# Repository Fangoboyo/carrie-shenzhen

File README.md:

# Carrie 🥕 — Embedded Audio/Video Recording Smart Pen

An embedded audio-recording smart pen shaped like a carrot, featuring a custom pot docking station for charging and data transfer. Powered by the Luckfox Pico Mini B (RV1103).

BILL OF MATERIALS IS IN [docs](/docs)

---

## Project Overview

A personal carry device in the shape of a carrot, Carrie is an interpretation of the carrot pen used by Judy Hopps in Zootopia. It's built with a microphone and a camera, integrated into the tiny form factor of a pen, and powered by an embedded Linux microcontroller (Luckfox Pico Mini B) on a custom PCB. With the click of a button, Carrie records 1080p footage at 30 FPS with audio, making sure you never forget to record those memorable moments. Then, simply take off the cap and plug the pen into the pot docking station to transfer your video files to a host computer and charge Carrie's battery.

---

## Why?

All 4 of the team members of this project are High School seniors. At the end of the year, many of the people who we have spent a majority of our lives with will be leaving to colleges across the world. It's easy to say that you'll keep in touch and commit to sending pictures and videos often of what you do everyday, but it's often a promise that is neglected not from a lack of care, but from the nature of experiencing an event; your first thought isn't always to start recording. With a personal carry device in such a form factor, Carrie serves as an always present, physical reminder of that promise. In this way, it helps old friends reconnect and stay connected.

---

## Directory Structure

```
├── docs/                           # Project documentation, Zines, and planning
│   ├── planning/                   # Vault planning notes and Technical Canvas
│   │   ├── notes/                  # Detailed engineering notes (display, GPIO, recording, etc.)
│   │   └── technical_overview.canvas # Visual concept overview
│   ├── bill_of_materials.csv       # Master Bill of Materials (BOM) with links & costs
│   └── zine.pdf                    # Creative project documentation
├── hardware/                       # Mechanical and Electrical designs
│   ├── cad/                        # Fusion 360 & STEP models
│   │   ├── individual_parts/       # Separate CAD files for components
│   │   └── README.md               # CAD specific notes & instructions
│   └── pcb/                        # KiCad PCB designs
│       ├── battery_charger/        # Carrot power regulation and battery charger PCB
│       ├── carry/                  # Main controller and breakout board PCB
│       ├── dirt/                   # Pot wiring junction PCB (V1)
│       └── dirt2/                  # Pot wiring junction PCB (V2)
├── firmware/                       # Source code for microcontrollers
│   ├── carrot/                     # RV1103 C code (Camera, Audio, and GPIO controls)
│   └── pot/                        # ESP8266 display driver code (.ino)
├── materials/                      # Detailed component datasheet notes & summaries
│   ├── bms/                        # Battery Management System notes (MCP73831, DW01A, etc.)
│   ├── images/                     # Component reference photos
│   └── *.md                        # Individual parts summaries (LCD, Microphone, Pogo, etc.)
└── platform/                       # React frontend & PocketBase/Bun backend dashboard
```

---

## Step-by-Step Build & Replication Guide

Follow this guide to replicate both the carrot pen (Carrie) and the docking station (Pot).

---

### 1. Bill of Materials (BOM)
Refer to the detailed master [Bill of Materials](docs/bill_of_materials.csv) for pricing, sourcing links, and specifications.

*   **Compute (Pen):** [Luckfox Pico Mini B (RV1103)](materials/esp32.md) - Linux SBC
*   **Sensor (Pen):** [SC3336 3MP Camera Module](materials/lcd_display.md) (CSI interface)
*   **Audio (Pen):** [SPH0655 Digital MEMS Microphone](materials/microphone.md)
*   **Battery (Pen):** 3.7V 800mAh Li-ion battery (size 14500 cell)
*   **Power (Pen):** Custom charger PCB with [MCP73831T-2A Charger IC](materials/bms/mcp73831.md)
*   **Indicator (Pen):** SunLED XZVGMDK53W-9 (bi-color Red/Green SMD LED)
*   **Compute (Pot):** [ESP8266 Dev Board](materials/esp32.md) (Wemos D1 Mini or similar)
*   **Display (Pot):** [ILI9341 320x240 SPI Touchscreen Display](materials/lcd_display.md)
*   **Docking Junction:** 4-pin Magnetic Contact POGO pins (5V, GND, D+, D-)
*   **Enclosure:** Orange/Green PLA filament, PLA glue.

---

### 2. Schematics & Electrical Design
The electrical system is divided between the Pen and the Pot. Schematics can be reviewed inside the [KiCad PCB Projects](hardware/pcb/).

#### A. The Pen (Carrie)
The pen uses two PCBs:
1.  **Main Board (`hardware/pcb/carry/`):** Hosts the Luckfox Pico Mini B. Routes the camera CSI ribbon, digital MEMS microphone (SPH0655), recording button, and status indicator LEDs.
2.  **Battery Charger Board (`hardware/pcb/battery_charger/`):** Features the [MCP73831T](materials/bms/mcp73831.md) charge controller, protection circuit (DW01A + FS8205A), and matches the bottom shape of the pen where the 4 magnetic contact pads reside.

##### Main Compute Module: Embedded Luckfox Pico Mini B

| Luckfox Pico Mini B (2D Layout) | Luckfox Pico Mini B (3D Render) |
| :---: | :---: |
|  |  |

*Figure 2: The RV1103-based Luckfox Pico Mini B development board used as the central Linux-based camera controller.*

##### Input: Audio & Video

| Microphone Breakout | CSI Camera Module |
| :---: | :---: |
|  |  |

*Figure 3: Layouts for the digital SPH0655 MEMS Microphone and the SC3336 3MP CSI camera module.*

##### Power Management: MCP73831T-2A

| Charge Controller Chip | 2D Layout Routing | 3D Board Design |
| :---: | :---: | :---: |
|  |  |  |

*Figure 4: The custom power board containing the MCP73831 charge management IC and protection circuits to safely regulate the 14500 Li-ion battery.*

##### Status Indicator: SunLED XZVGMDK53W-9

*Figure 5: Bi-color (Red/Green) SMD status indicator LED for tracking recording states.*

---

#### B. The Pot (Docking Station)
The pot PCB (`hardware/pcb/dirt2/`) aggregates connections for the ESP8266 Dev Board, ILI9341 SPI Display, and a Y-Junction cable to split power and USB data signals.

##### Embedded ESP8266 Board

| 3D Model | 2D Design |
| :---: | :---: |
|  |  |

*Figure 6: Custom PCB interface housing the ESP8266, routing signals to the LCD and decoupling incoming USB lines.*

##### Display: ILI9341

*Figure 7: SPI Serial TFT display used to display system telemetry and connection feedback.*

---

### 3. CAD & Mechanical Assembly
All model assets are stored in [hardware/cad/](hardware/cad/).

#### The Shell

| Camera Side Cutout | Button Side Cutout |
| :---: | :---: |
|  |  |

*Figure 8: Outer mechanical CAD model of the carrot-shaped casing showing camera aperture and button positioning.*

#### Internals

*Figure 9: Exploded and internal CAD views highlighting the structural ribs, battery clip, and PCB slots inside the carrot pen.*

#### Flowerpot Dock

| Isometric View | Front Cutaway | Back Enclosure |
| :---: | :---: | :---: |
|  |  |  |

| Display Bezel Fitting | Base Enclosure Layout | Underneath Routing |
| :---: | :---: | :---: |
|  |  |  |

| Receptacle Neck Alignment | | |
| :---: | :---: | :---: |
|  | | |

*Figure 10: Assembly CAD breakdowns of the flowerpot dock housing the display, wiring channels, and internal board mounts.*

#### POGO Pins for Data Transfer
We use a magnetic, spring-loaded POGO pin port at the bottom interface of the carrot and inside the pot neck to route data and charge signals.

*Figure 11: The 4-pin magnetic layout routing 5V, GND, D+, and D- for toolless charging and storage connection.*

---

### 4. Firmware Build & Flashing Guide

#### A. Pen Firmware (RV1103)
The pen runs Buildroot Linux. Its C firmware is compiled inside a Docker Dev Container to manage target environment dependencies.

1.  **Launch Container:**
    Open the [firmware/carrot/](firmware/carrot/) directory in VS Code. It will prompt you to reopen in the dev container. Under the hood, this loads the `Dockerfile` from [firmware/carrot/.devcontainer/Dockerfile](firmware/carrot/.devcontainer/Dockerfile) which installs the cross-compiler toolchain `arm-rockchip830-linux-uclibcgnueabihf` and Rockchip Media Process Interface (RKMPI) headers.
2.  **Build Code:**
    Run the compile script:
    ```bash
    ./build.sh main
    ```
    This script cross-compiles:
    *   `main.c` (Core thread controller)
    *   `gpio/gpio.c` (Button interrupt and state control)
    *   `recorder/camera_recorder.c` (Uses RKMPI to fetch H.264 video streams from hardware framebuffers)
3.  **Deployment via ADB:**
    The script automatically runs `adb push` over the USB bridge to load the executable into the Luckfox:
    ```bash
    # Pushes binary and marks executable
    adb push main /root/
    adb shell "chmod +x /root/main"
    ```
    To test instantly, run:
    ```bash
    adb shell /root/main
    ```

#### B. Pot Display Firmware (ESP8266)
1.  Open the [firmware/pot/](firmware/pot/) folder in Arduino IDE.
2.  Install the **TFT_eSPI** library through the Library Manager.
3.  Copy/configure the correct pin assignments (CS, DC, RST, LED) in the `User_Setup.h` file located inside the `TFT_eSPI` library folder directory to match the ESP8266 pinout.
4.  Build and upload [displaydriver.ino](firmware/pot/displaydriver.ino) to your ESP8266 over serial USB.

---

### 5. Testing & Verification

1.  **Hardware Self-Test:** Connect the carrot pen to your PC. A solid green light indicates full charge; red/orange indicates active charging.
2.  **GPIO Check:** Run the compiled binary [gpio_input](firmware/carrot/gpio/gpio_input.c) to verify button state changes:
    ```bash
    ./build.sh gpio
    ```
3.  **Video Stream Test:** Run the `recorder` profile to verify image sensor capture and H.264 stream writing:
    ```bash
    ./build.sh recorder
    # Run on board: adb shell /root/camera_recorder_demo
    ```
4.  **Full Loop Recording:** Tap the physical button on the carrot casing. The indicator LED flashes to signal recording. Push the button again to stop.
5.  **Docking & Transfer:** Dock the pen in the Pot. The LCD screen should light up, showing connection telemetry. The PC will recognize a USB mass storage device or an ADB network interface. 
6.  **Web Dashboard Sync:** Start the React platform. Use the dashboard to fetch files from the docked pen and stream them directly onto Google Drive.
### Web Platform Dashboard
Okay I'm going to cut the formal documentation-speech for this part because im genuinely so proud of this website, it lets you plug your pot directly into your computer, and the browser is able to take the datastream from the USB and directly upload it to youtube for infinite free storage. All of the components are super animated like the books float and flip on their own, they rotate, they blur, all done with just tailwind. It genuinely took such a long time but adds an incredibly integrated aspect of the project that just brings everything together.

*Figure 1: React-based web dashboard displaying scrapbook video feeds synced from the carrot pen.*

For more details on the design, code operations, and custom hardware modules, see the docs folder, where obsidian canvases draw out everything overviewing the project.

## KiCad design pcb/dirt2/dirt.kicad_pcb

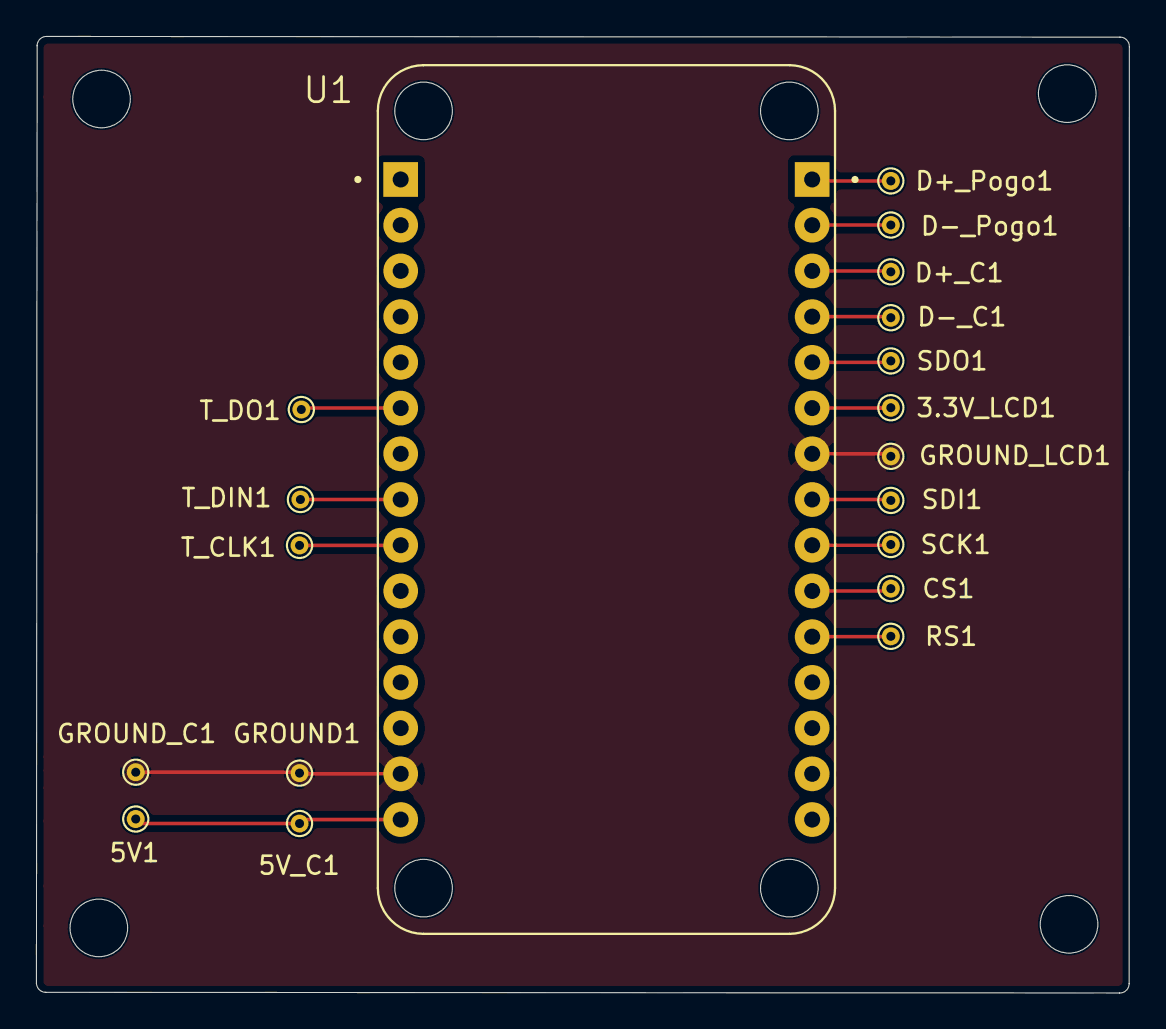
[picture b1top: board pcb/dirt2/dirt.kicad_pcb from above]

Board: 2 copper layers, 60.7 x 53.1 mm, 19 parts (0 on the bottom side), 15 nets.

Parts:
3.3V_LCD1: 3.3V Output to LCD; TestPoint_THTPad_D1.0mm_Drill0.5mm
5V1: 5V Output from Pogo; TestPoint_THTPad_D1.0mm_Drill0.5mm
5V_C1: 5V Input USB C; TestPoint_THTPad_D1.0mm_Drill0.5mm
CS1: TestPoint; TestPoint_THTPad_D1.0mm_Drill0.5mm
D+_C1: D+ FROM USB C; TestPoint_THTPad_D1.0mm_Drill0.5mm
D+_Pogo1: D+ FROM Pogo; TestPoint_THTPad_D1.0mm_Drill0.5mm
D-_C1: D- FROM USB C; TestPoint_THTPad_D1.0mm_Drill0.5mm
D-_Pogo1: D- FROM Pogo; TestPoint_THTPad_D1.0mm_Drill0.5mm
GROUND1: GND from Pogo; TestPoint_THTPad_D1.0mm_Drill0.5mm
GROUND_C1: GND from USB C; TestPoint_THTPad_D1.0mm_Drill0.5mm
GROUND_LCD1: GND to LCD; TestPoint_THTPad_D1.0mm_Drill0.5mm
RS1: TestPoint; TestPoint_THTPad_D1.0mm_Drill0.5mm
SCK1: TestPoint; TestPoint_THTPad_D1.0mm_Drill0.5mm
SDI1: TestPoint; TestPoint_THTPad_D1.0mm_Drill0.5mm
SDO1: TestPoint; TestPoint_THTPad_D1.0mm_Drill0.5mm
T_CLK1: TestPoint; TestPoint_THTPad_D1.0mm_Drill0.5mm
T_DIN1: TestPoint; TestPoint_THTPad_D1.0mm_Drill0.5mm
T_DO1: TestPoint; TestPoint_THTPad_D1.0mm_Drill0.5mm
U1: SEEED_113990105

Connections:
GND: GROUND1.1 (1_1), GROUND_C1.1 (1_1), GROUND_LCD1.1 (1_1), U1.J1_14 (GND), U1.J2_7 (GND)
unnamed: 3.3V_LCD1.1 (1_1), U1.J2_6 (3v3)
unnamed: T_CLK1.1 (1_1), U1.J1_9 (CLK)
unnamed: D+_Pogo1.1 (1_1), U1.J2_1 (D0)
unnamed: D-_Pogo1.1 (1_1), U1.J2_2 (D1)
unnamed: D+_C1.1 (1_1), U1.J2_3 (D2)
unnamed: D-_C1.1 (1_1), U1.J2_4 (D3)
unnamed: SDO1.1 (1_1), U1.J2_5 (D4)
unnamed: SDI1.1 (1_1), U1.J2_8 (D5)
unnamed: SCK1.1 (1_1), U1.J2_9 (D6)
unnamed: CS1.1 (1_1), U1.J2_10 (D7)
unnamed: RS1.1 (1_1), U1.J2_11 (D8)
unnamed: T_DIN1.1 (1_1), U1.J1_8 (SD0)
unnamed: T_DO1.1 (1_1), U1.J1_6 (SD1)
unnamed: 5V1.1 (1_1), 5V_C1.1 (1_1), U1.J1_15 (Vin)

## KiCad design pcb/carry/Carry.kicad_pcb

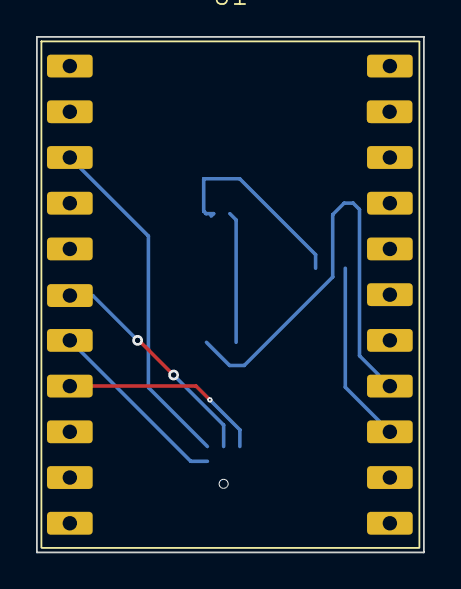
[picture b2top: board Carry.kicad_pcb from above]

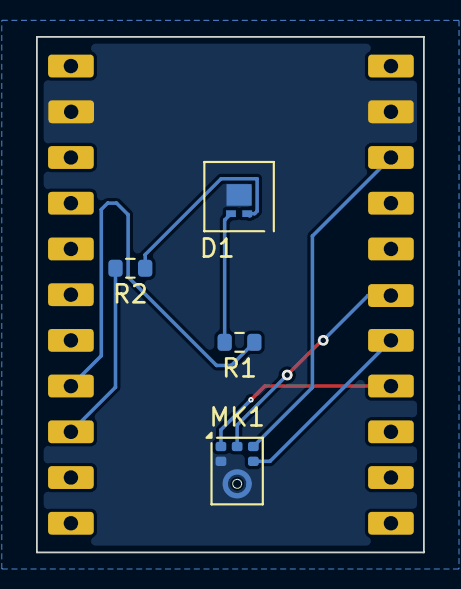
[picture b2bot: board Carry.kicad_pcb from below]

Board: 2 copper layers, 21.5 x 28.6 mm, 5 parts (4 on the bottom side), 9 nets.

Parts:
D1: LED_Dual_KKA; LED-L1T2_LUMILEDS
MK1: SPH0645LM4H; Knowles_SPH0645LM4H-6_3.5x2.65mm
R1, R2: 1k; R_0603_1608Metric
U1: Luckfox-Pico_Mini_B; Luckfox_Pico_Mini_B

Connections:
/MIC_DATA: MK1.6 (DATA), U1.6 (GPIO1_C0_d)
GND: D1.3 (K), MK1.2 (SEL), MK1.3 (GND), U1.2 (GND), U1.21 (GND)
unnamed: D1.1 (A1), R2.1
unnamed: D1.2 (A2), R1.2
unnamed: MK1.4 (BCLK), U1.7 (GPIO1_C1_d)
unnamed: MK1.5 (VDD), U1.3 (VCC_3V3)
unnamed: MK1.1 (WS), U1.8 (GPIO1_C2_d)
unnamed: R2.2, U1.14 (GPIO1_D2_d)
unnamed: R1.1, U1.15 (GPIO1_D3_d)

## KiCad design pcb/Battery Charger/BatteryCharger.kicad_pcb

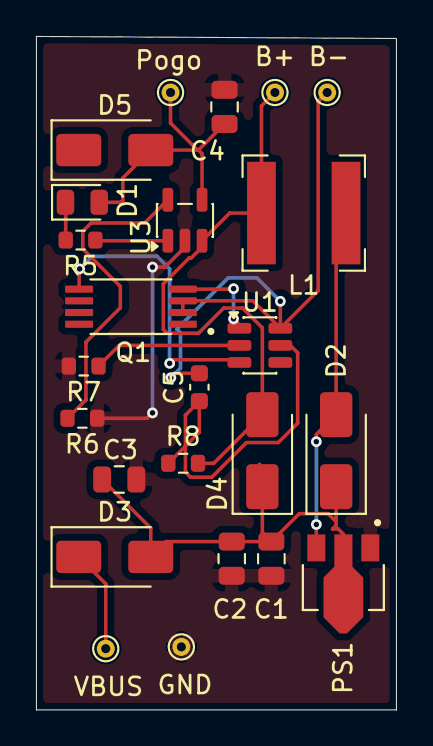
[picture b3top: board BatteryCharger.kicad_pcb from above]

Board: 2 copper layers, 20.0 x 37.4 mm, 24 parts (0 on the bottom side), 14 nets.

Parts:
B+: B+; TestPoint_THTPad_D1.0mm_Drill0.5mm
B-: B-; TestPoint_THTPad_D1.0mm_Drill0.5mm
C1, C2: 12; C_0805_2012Metric
C3, C4: 4.7; C_0805_2012Metric
C5: 0.1; C_0603_1608Metric
D1: LED; LED_0805_2012Metric
D2, D3, D4, D5: SS14; D_SMA
GND: B-; TestPoint_THTPad_D1.0mm_Drill0.5mm
L1: 22; L_Bourns-SRN6028
PS1: ME2108A33P
Pogo: Pogo+; TestPoint_THTPad_D1.0mm_Drill0.5mm
Q1: FS8205A
R5: 470; R_0603_1608Metric
R6: 2k; R_0603_1608Metric
R7: 1k; R_0603_1608Metric
R8: 100; R_0603_1608Metric
U1: DW01A; SOT-23-6
U3: MCP73831; SOT-23-5
VBUS: Output 5V; TestPoint_THTPad_D1.0mm_Drill0.5mm

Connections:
GND: C1.2, C2.2, C3.2, C4.2, GND.1 (1_1), PS1.1 (VSS), Q1.6, Q1.7, R6.1, R7.2, U3.2 (V_{SS})
unnamed: C4.1, D1.2 (A), D5.2 (A), Pogo.1 (1_1), U3.4 (V_{DD})
unnamed: D1.1 (K), R5.2
unnamed: D2.2 (A), L1.2, PS1.3 (LX)
unnamed: C1.1, C2.1, C3.1, D2.1 (K), D3.2 (A), D4.1 (K), PS1.2 (VOUT)
unnamed: D3.1 (K), D5.1 (K), VBUS.1 (1_1)
unnamed: B+.1 (1_1), D4.2 (A), L1.1, R8.1, U3.3 (V_{BAT})
unnamed: R7.1, U1.2 (CS)
unnamed: B-.1 (1_1), C5.2, Q1.2, Q1.3, U1.6 (GND)
unnamed: Q1.5, U1.3 (OC)
unnamed: Q1.4, U1.1 (OD)
unnamed: C5.1, R8.2, U1.5 (VCC)
unnamed: R6.2, U3.5 (PROG)
unnamed: R5.1, U3.1 (STAT)

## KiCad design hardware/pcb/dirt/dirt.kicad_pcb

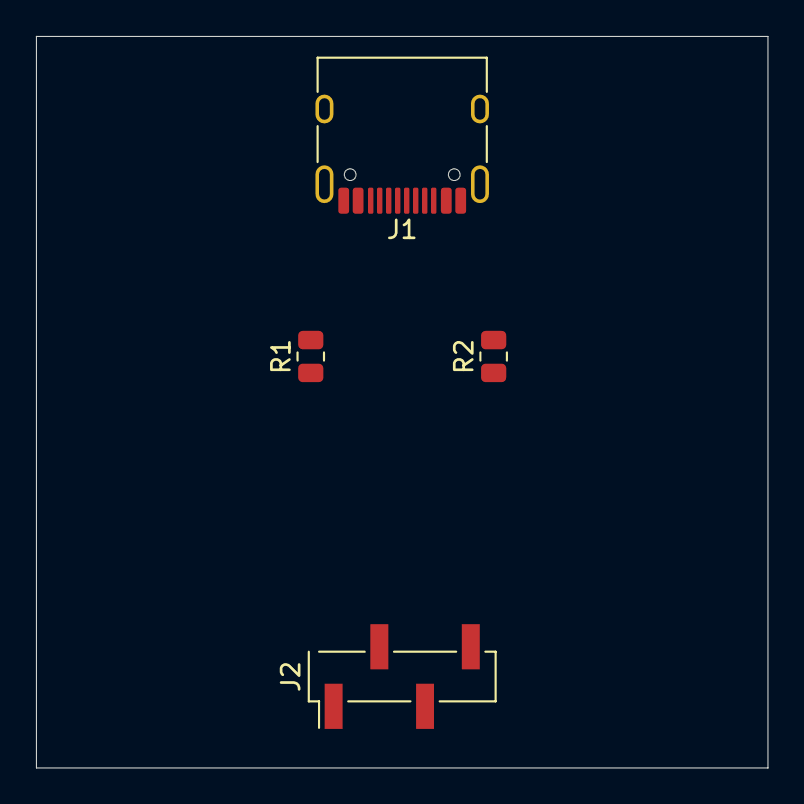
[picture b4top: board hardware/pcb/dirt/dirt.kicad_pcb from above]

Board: 2 copper layers, 40.6 x 40.6 mm, 4 parts (0 on the bottom side), 6 nets, no tracks yet.

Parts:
J1: USB_C_Receptacle_USB2.0_16P; USB_C_Receptacle_HRO_TYPE-C-31-M-12
J2: Conn_01x04_Pin; PinHeader_1x04_P2.54mm_Vertical_SMD_Pin1Left
R1, R2: 5.1k; R_0805_2012Metric

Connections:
GND: J1.A1 (GND), J1.A12 (GND), J1.B1 (GND), J1.B12 (GND), J1.SH (SHIELD), J2.4, R1.2, R2.2
unnamed: J1.A5 (CC1), R1.1
unnamed: J1.B5 (CC2), R2.1
unnamed: J1.A4 (VBUS), J1.A9 (VBUS), J1.B4 (VBUS), J1.B9 (VBUS), J2.1
unnamed: J1.A7 (D-), J1.B7 (D-), J2.2
unnamed: J1.A6 (D+), J1.B6 (D+), J2.3

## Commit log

2026-05-30 recommit all firmware/software files
2026-05-31 Dirt made my me
    Um this is really rudimentary, but this is just the schematic for the dirt pile. I have the footprint for the microcontroller as well.
2026-06-02 UH
    wait now its here i think
2026-06-03 update css animations and added obsidian vault files
2026-06-03 bill of materials update
2026-06-04 ChargerBreakoutBoard
    uh i just tried to design something, I do not know if it works.
2026-06-05 I added the 2 extra components to the battery regulator
2026-06-07 type shiii
    I added the booster converter
2026-06-10 stuff i think
2026-06-14 i just made some changes
2026-06-15 Rough Draft FINISHED
2026-06-16 uh
    asdfasdfasdf
2026-06-17 Revise README
2026-06-18 website update im kms
2026-06-18 i created some edits and added the zine
2026-06-18 Enhance README with project details and purpose
    Expanded project overview and added motivation for development.
2026-06-18 stuff it hink
2026-06-18 charger has been finished final draft
2026-06-18 dirt finished
2026-06-18 finished all PCB awaiting checkup
2026-06-18 added cad shit
2026-06-19 more site stuff + zine/BOM
2026-06-19 Update README with hardware architecture details
2026-06-19 Update README with shell and display information
    Added sections for shell and display details, including images and hardware architecture.
2026-06-19 website is finished
2026-06-19 Update README with software and hardware details
    Added sections on software, firmware, and hardware architecture for the carrot pen and pot. Included details on power management, data transfer, and display components.
2026-06-19 Enhance website section with tech stack information
    Added details about the backend and frontend technologies used for the website.
2026-06-19 fix for submission prescan
2026-06-23 Enhance README with project overview and image
    Added introductory text and image to README.
2026-06-23 Revise Web Platform Dashboard details in README
    Updated the Web Platform Dashboard section with new features and removed redundant content.
2026-06-23 Add bill of materials reference to README
    Added a reference to the bill of materials in the documentation.
2026-06-25 stuff
    Removed comments and cleaned up code in display driver.
2026-06-25 yo i forgor to delete the template readme lol
    deleted template readme and rework some docs to be less boilerplated
2026-06-25 Restore README.md and bill of materials from origin/main, retaining local comment cleanups
2026-06-25 i screwed up the git but i got it fixed now i delete readme
2026-06-25 remove redundant elements
